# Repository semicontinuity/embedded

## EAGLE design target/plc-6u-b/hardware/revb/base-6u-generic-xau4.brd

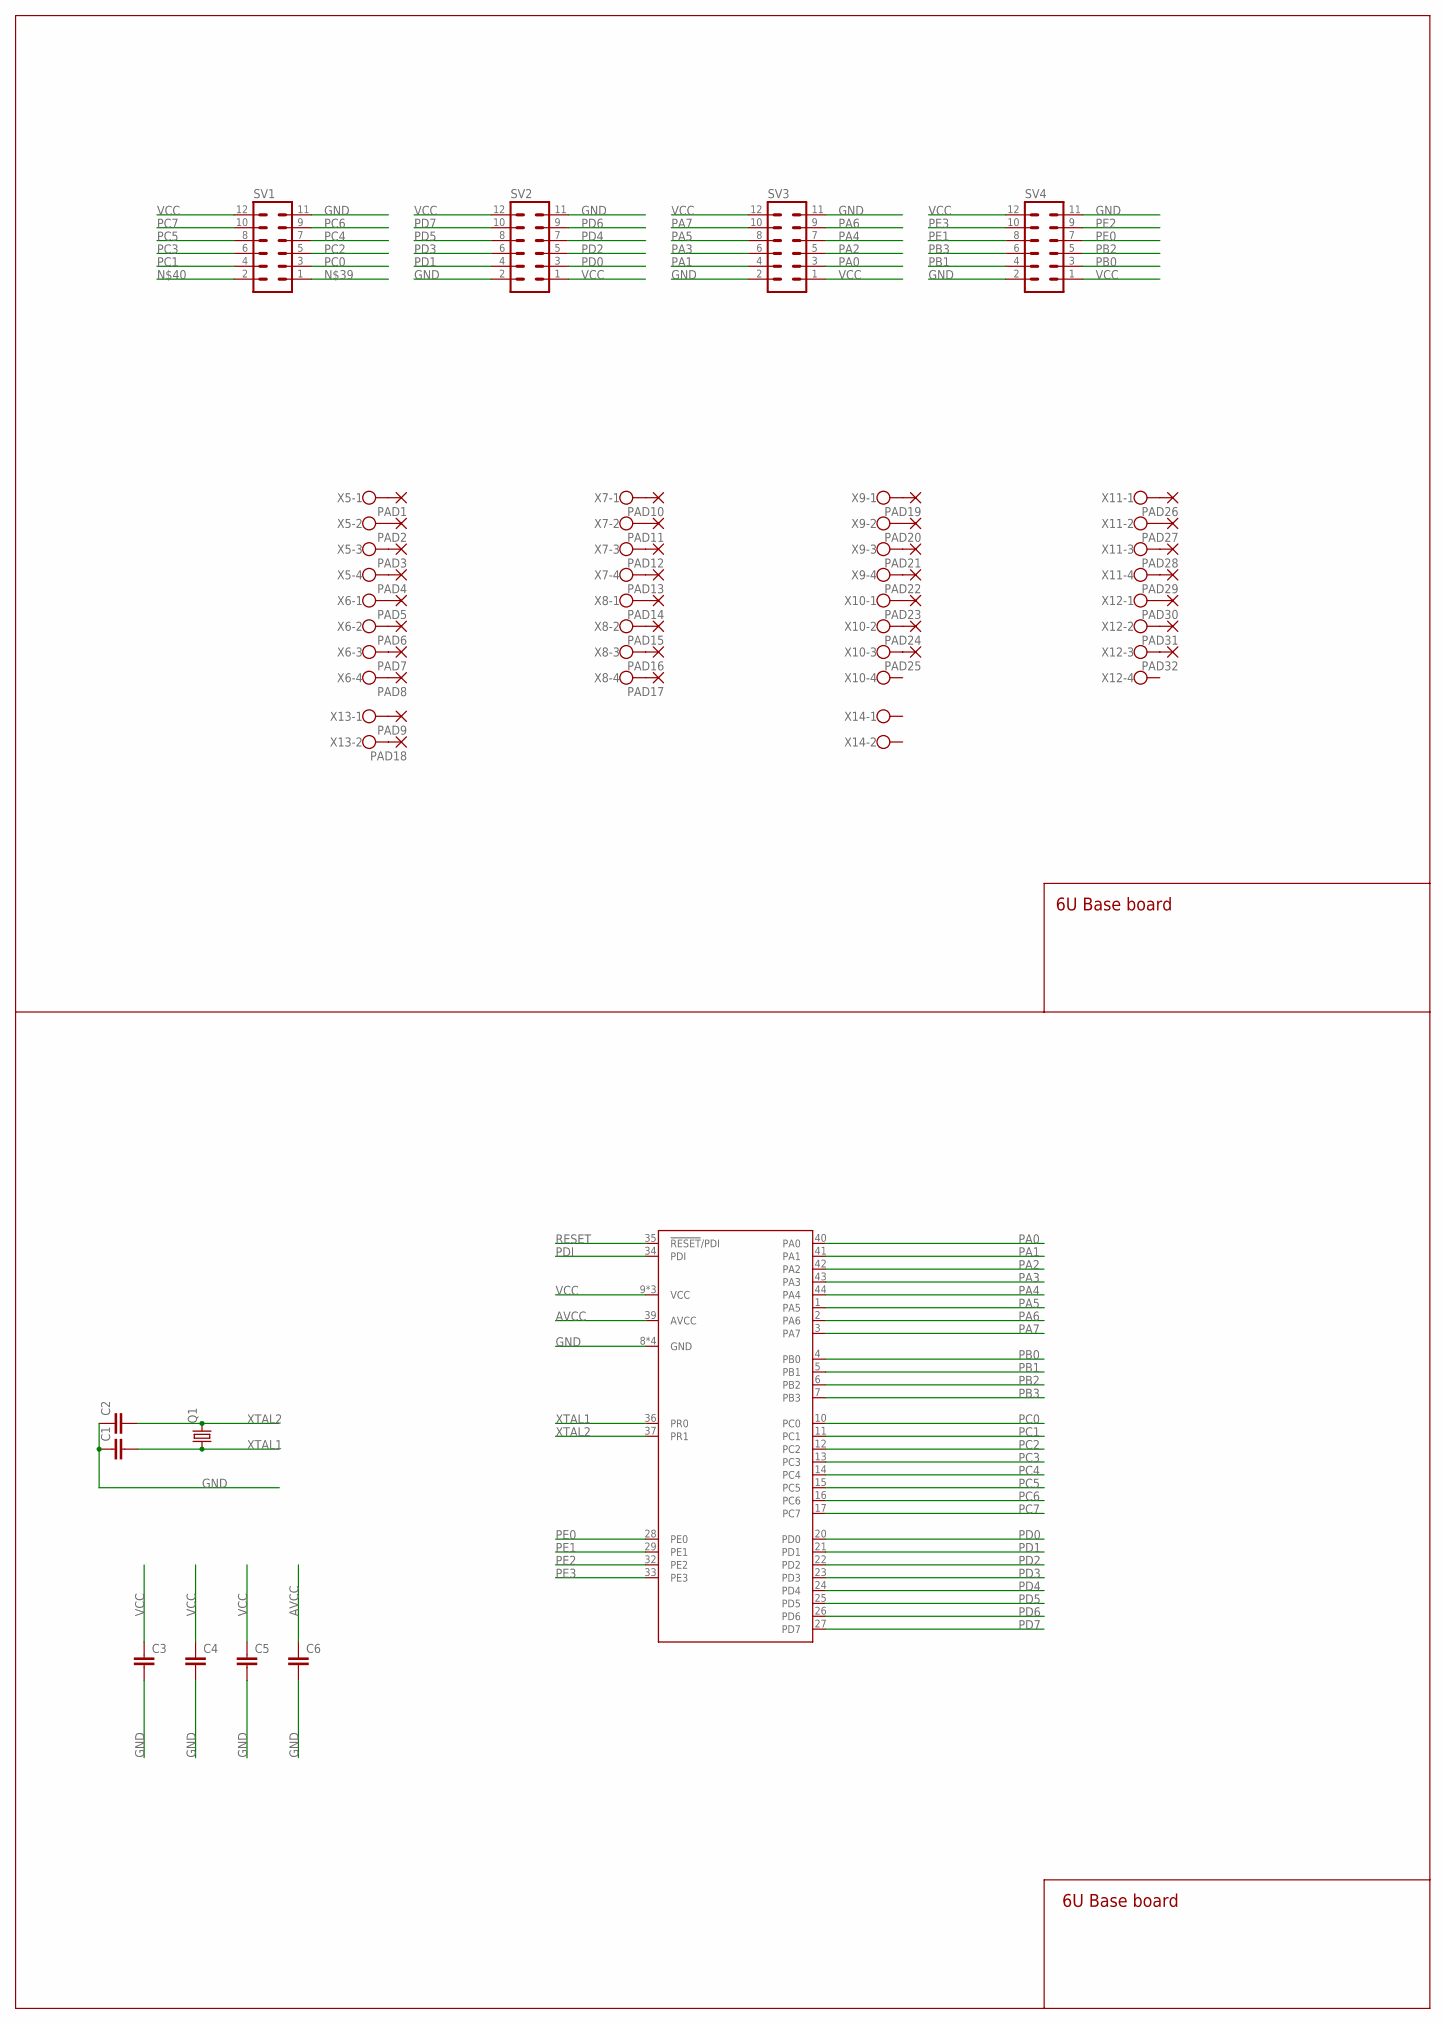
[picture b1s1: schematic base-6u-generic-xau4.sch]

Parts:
C1, C2: C-EUC0805; C0805
C3, C4, C5, C6: C-EUC0603; C0603
PAD1, PAD2, PAD3, PAD4, PAD5, PAD6, PAD7, PAD8, PAD9, PAD10, PAD11, PAD12, PAD13, PAD14, PAD15, PAD16, PAD17, PAD18, PAD19, PAD20, PAD21, PAD22, PAD23, PAD24, PAD25, PAD26, PAD27, PAD28, PAD29, PAD30, PAD31, PAD32: 2,54/0,8
Q1: CRYSTALHC49S; HC49/S
SV1, SV2, SV3, SV4: MA06-2
U1: ATXMEGA32A4U-AU; TQFP-44A-44
X5, X6, X7, X8, X9, X10, X11, X12: W237-4
X13, X14: W237-102

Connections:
AVCC: C6.1, U1.39 (AVCC)
GND: C1.1, C2.1, C3.2, C4.2, C5.2, C6.2, SV1.11, SV2.2, SV2.11, SV3.2, SV3.11, SV4.2, SV4.11, U1.8 (GND), U1.18 (GND), U1.30 (GND), U1.38 (GND)
unnamed: PAD1.1, X5.1
unnamed: PAD2.1, X5.2
unnamed: PAD3.1, X5.3
unnamed: PAD4.1, X5.4
unnamed: PAD5.1, X6.1
unnamed: PAD6.1, X6.2
unnamed: PAD7.1, X6.3
unnamed: PAD8.1, X6.4
unnamed: PAD9.1, X13.1
unnamed: PAD10.1, X7.1
unnamed: PAD11.1, X7.2
unnamed: PAD12.1, X7.3
unnamed: PAD13.1, X7.4
unnamed: PAD14.1, X8.1
unnamed: PAD15.1, X8.2
unnamed: PAD16.1, X8.3
unnamed: PAD17.1, X8.4
unnamed: PAD18.1, X13.2
unnamed: PAD26.1, X11.1
unnamed: PAD27.1, X11.2
unnamed: PAD28.1, X11.3
unnamed: PAD29.1, X11.4
unnamed: PAD30.1, X12.1
unnamed: PAD31.1, X12.2
unnamed: PAD32.1, X12.3
unnamed: PAD19.1, X9.1
unnamed: PAD20.1, X9.2
unnamed: PAD21.1, X9.3
unnamed: PAD22.1, X9.4
unnamed: PAD23.1, X10.1
unnamed: PAD24.1, X10.2
unnamed: PAD25.1, X10.3
PA0: SV3.3, U1.40 (PA0)
PA1: SV3.4, U1.41 (PA1)
PA2: SV3.5, U1.42 (PA2)
PA3: SV3.6, U1.43 (PA3)
PA4: SV3.7, U1.44 (PA4)
PA5: SV3.8, U1.1 (PA5)
PA6: SV3.9, U1.2 (PA6)
PA7: SV3.10, U1.3 (PA7)
PB0: SV4.3, U1.4 (PB0)
PB1: SV4.4, U1.5 (PB1)
PB2: SV4.5, U1.6 (PB2)
PB3: SV4.6, U1.7 (PB3)
PC0: SV1.3, U1.10 (PC0)
PC1: SV1.4, U1.11 (PC1)
PC2: SV1.5, U1.12 (PC2)
PC3: SV1.6, U1.13 (PC3)
PC4: SV1.7, U1.14 (PC4)
PC5: SV1.8, U1.15 (PC5)
PC6: SV1.9, U1.16 (PC6)
PC7: SV1.10, U1.17 (PC7)
PD0: SV2.3, U1.20 (PD0)
PD1: SV2.4, U1.21 (PD1)
PD2: SV2.5, U1.22 (PD2)
PD3: SV2.6, U1.23 (PD3)
PD4: SV2.7, U1.24 (PD4)
PD5: SV2.8, U1.25 (PD5)
PD6: SV2.9, U1.26 (PD6)
PD7: SV2.10, U1.27 (PD7)
PDI: U1.34 (PDI)
PE0: SV4.7, U1.28 (PE0)
PE1: SV4.8, U1.29 (PE1)
PE2: SV4.9, U1.32 (PE2)
PE3: SV4.10, U1.33 (PE3)
RESET: U1.35 (!RESET!/PDI)
VCC: C3.1, C4.1, C5.1, SV1.12, SV2.1, SV2.12, SV3.1, SV3.12, SV4.1, SV4.12, U1.9 (VCC), U1.19 (VCC), U1.31 (VCC)
XTAL1: C1.2, Q1.1, U1.36 (PR0)
XTAL2: C2.2, Q1.2, U1.37 (PR1)

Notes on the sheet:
6U Base board

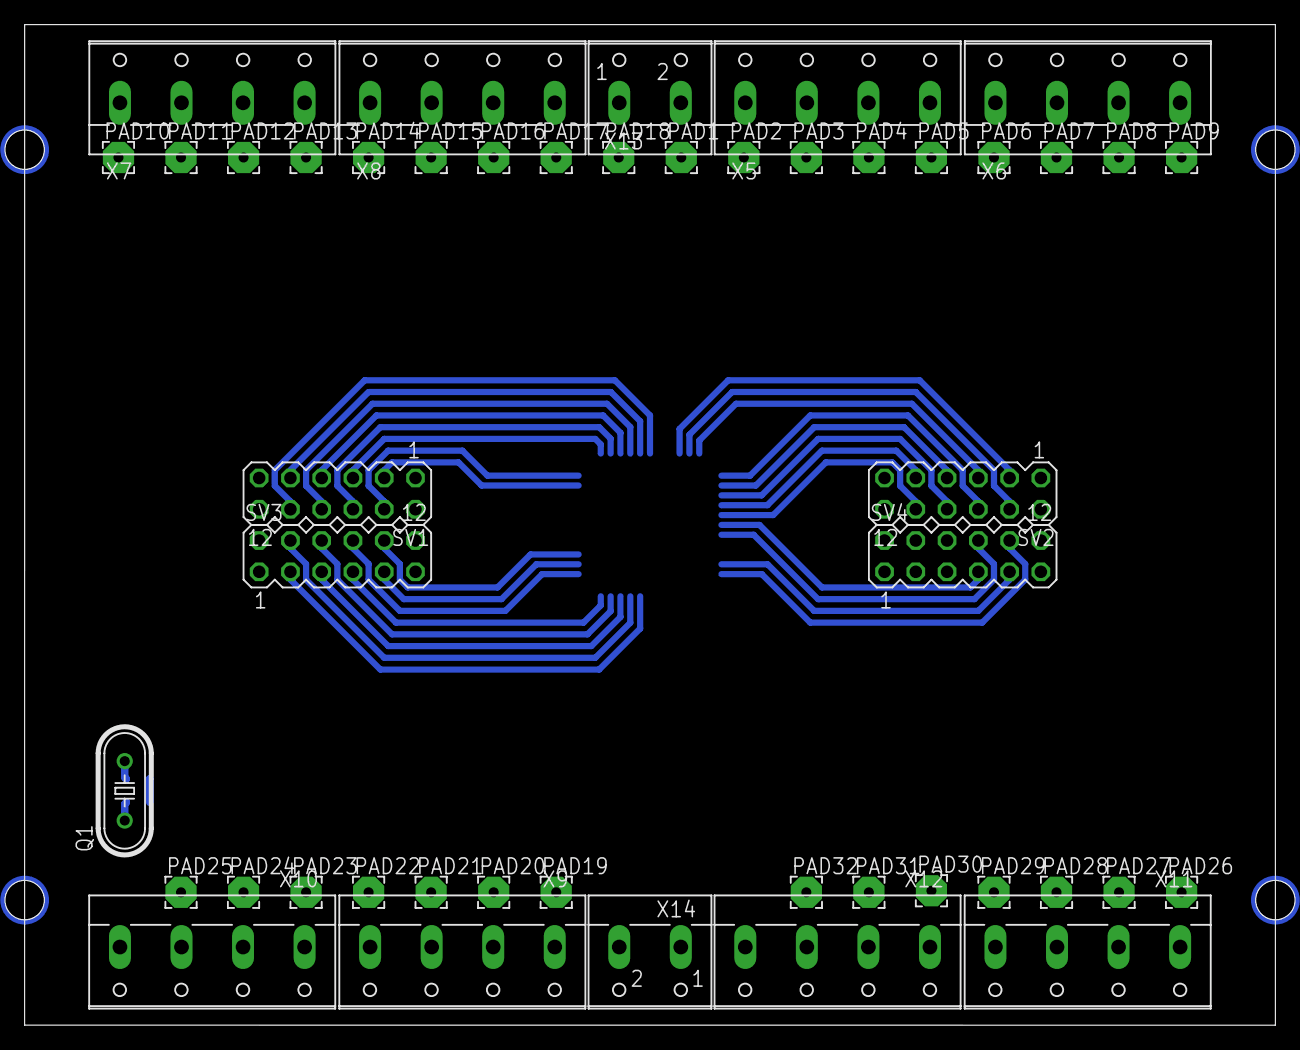
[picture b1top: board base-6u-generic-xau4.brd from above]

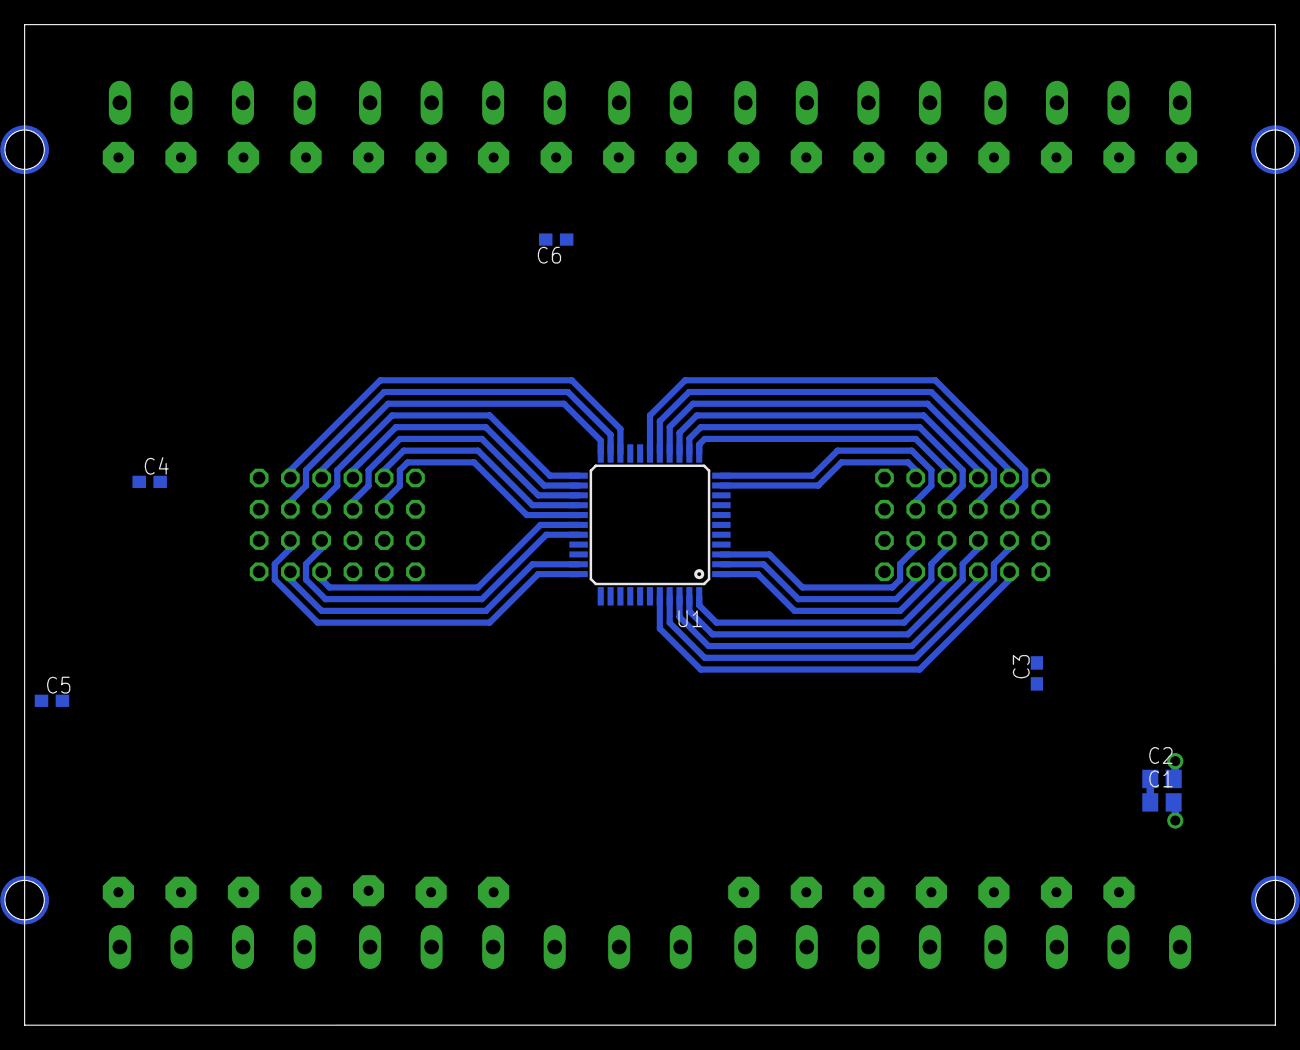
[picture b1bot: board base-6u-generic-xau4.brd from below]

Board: 2 copper layers, 101.6 x 81.3 mm, 54 parts (7 on the bottom side), 69 nets.

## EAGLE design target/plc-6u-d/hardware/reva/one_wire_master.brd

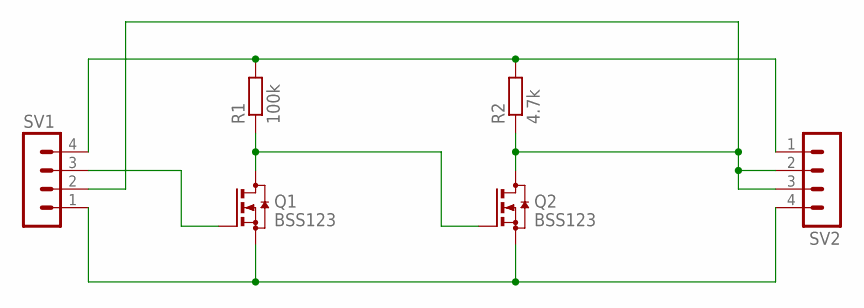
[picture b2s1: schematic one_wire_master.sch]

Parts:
Q1, Q2: BSS123; SOT23
R1: 100k; M0805
R2: 4.7k; M0805
SV1, SV2: MA04-1

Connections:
GND: Q1.2 (S), Q2.2 (S), SV1.1, SV2.4
IN: Q1.1 (G), SV1.3
unnamed: Q1.3 (D), Q2.1 (G), R1.1
OW: Q2.3 (D), R2.1, SV1.2, SV2.2, SV2.3
VCC: R1.2, R2.2, SV1.4, SV2.1

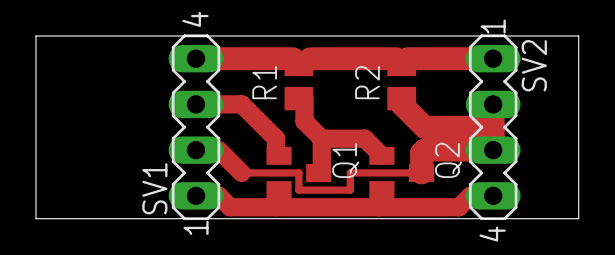
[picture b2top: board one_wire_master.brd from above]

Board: 2 copper layers, 30.1 x 10.2 mm, 6 parts (0 on the bottom side), 5 nets.

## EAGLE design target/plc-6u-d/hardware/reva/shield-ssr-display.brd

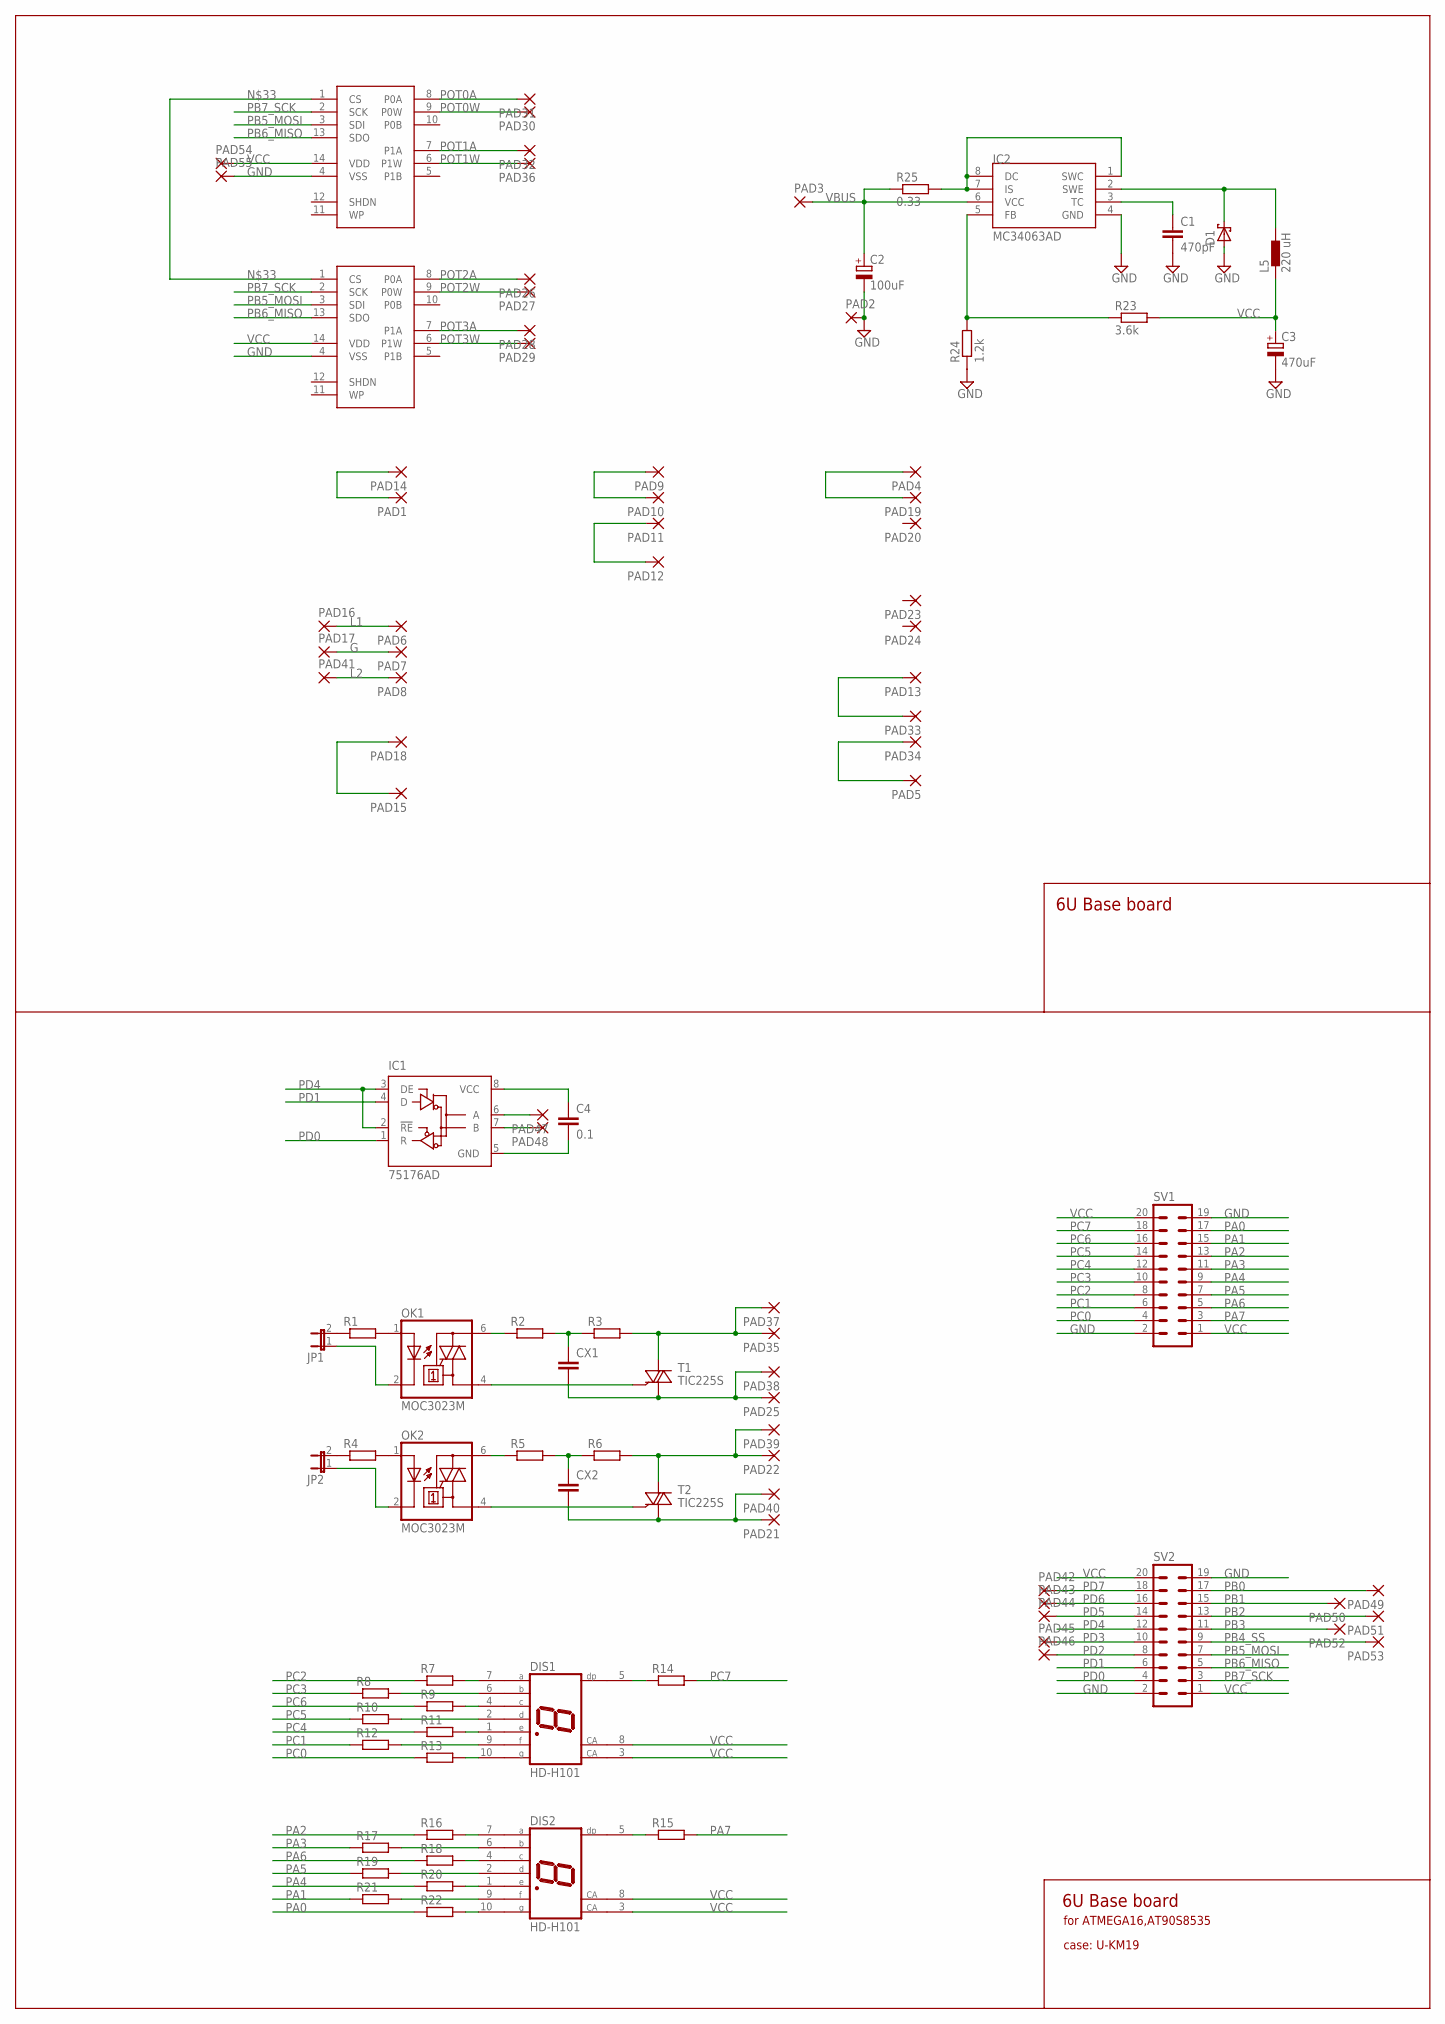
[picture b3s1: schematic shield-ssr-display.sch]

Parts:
C1: 470pF; C0805
C2: 100uF; E3,5-8
C3: 470uF; E3,5-8
C4: 0.1; C0805
CX1, CX2: CXXC15B5; XC15B5
D1: SCHOTTKY-DIODESMD; SMB
DIS1, DIS2: HD-H101; HDSP-M
IC1: 75176AD; D_R-PDSO-G8
IC2: MC34063AD; SOIC8
JP1, JP2: JP1E; JP1
L5: 220 uH; DR1030
OK1, OK2: MOC3023M; DIL06
PAD1, PAD2, PAD3, PAD4, PAD5, PAD6, PAD7, PAD8, PAD9, PAD10, PAD11, PAD12, PAD13, PAD14, PAD15, PAD16, PAD17, PAD18, PAD19, PAD20, PAD21, PAD22, PAD23, PAD24, PAD25, PAD26, PAD27, PAD28, PAD29, PAD30, PAD31, PAD32, PAD33, PAD34, PAD35, PAD36, PAD37, PAD38, PAD39, PAD40, PAD41: 2,54/0,8
PAD42, PAD43, PAD44, PAD45, PAD46, PAD47, PAD48, PAD49, PAD50, PAD51, PAD52, PAD53, PAD54, PAD55: 1,6/0,8
R1, R4: R-EU_M0805; M0805
R2, R3, R5, R6: R-EU_R1206; R1206
R7, R8, R9, R10, R11, R12, R13, R14, R15, R16, R17, R18, R19, R20, R21, R22: R-EU_R0603; R0603
R23: 3.6k; R0805
R24: 1.2k; R0805
R25: 0.33; R1206
SV1, SV2: MA10-2
T1, T2: TIC225S; TO220DS
U$1, U$2: MCP4231-DIP; DIL14

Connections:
G: PAD7.1, PAD17.1
GND: C1.2, C2.-, C3.-, C4.2, D1.A, IC1.5 (GND), IC2.4 (GND), PAD2.1, PAD4.1, PAD19.1, PAD55.1, R24.1, SV1.2, SV1.19, SV2.2, SV2.19, U$1.4 (VSS), U$2.4 (VSS)
L1: PAD6.1, PAD16.1
L2: PAD8.1, PAD41.1
unnamed: OK1.1 (A), R1.2
unnamed: JP1.2, R1.1
unnamed: JP1.1, OK1.2 (C)
unnamed: OK1.6 (A2), R2.1
unnamed: CX1.1, R2.2, R3.1
unnamed: OK1.4 (A1), T1.G
unnamed: PAD35.1, PAD37.1, R3.2, T1.A2
unnamed: CX1.2, PAD25.1, PAD38.1, T1.A1
unnamed: OK2.1 (A), R4.2
unnamed: JP2.2, R4.1
unnamed: JP2.1, OK2.2 (C)
unnamed: OK2.6 (A2), R5.1
unnamed: OK2.4 (A1), T2.G
unnamed: PAD22.1, PAD39.1, R6.2, T2.A2
unnamed: DIS1.7 (A), R7.2
unnamed: CX2.1, R5.2, R6.1
unnamed: CX2.2, PAD21.1, PAD40.1, T2.A1
unnamed: DIS1.6 (B), R8.2
unnamed: DIS1.4 (C), R9.2
unnamed: DIS1.2 (D), R10.2
unnamed: DIS1.1 (E), R11.2
unnamed: DIS1.9 (F), R12.2
unnamed: DIS1.10 (G), R13.2
unnamed: DIS1.5 (DP), R14.1
unnamed: DIS2.7 (A), R16.2
unnamed: DIS2.6 (B), R17.2
unnamed: DIS2.4 (C), R18.2
unnamed: DIS2.2 (D), R19.2
unnamed: DIS2.1 (E), R20.2
unnamed: DIS2.9 (F), R21.2
unnamed: DIS2.10 (G), R22.2
unnamed: DIS2.5 (DP), R15.1
unnamed: U$1.1 (CS), U$2.1 (CS)
unnamed: IC2.1 (SWC), IC2.7 (IS), IC2.8 (DC), R25.2
unnamed: PAD9.1, PAD10.1
unnamed: PAD11.1, PAD12.1
unnamed: D1.C, IC2.2 (SWE), L5.2
unnamed: C1.1, IC2.3 (TC)
unnamed: IC1.6 (A), PAD47.1
unnamed: IC2.5 (FB), R23.1, R24.2
unnamed: PAD13.1, PAD33.1
unnamed: PAD15.1, PAD18.1
unnamed: PAD1.1, PAD14.1
unnamed: IC1.7 (B), PAD48.1
PA0: R22.1, SV1.17
PA1: R21.1, SV1.15
PA2: R16.1, SV1.13
PA3: R17.1, SV1.11
PA4: R20.1, SV1.9
PA5: R19.1, SV1.7
PA6: R18.1, SV1.5
PA7: R15.2, SV1.3
PB0: PAD49.1, SV2.17
PB1: PAD50.1, SV2.15
PB2: PAD51.1, SV2.13
PB3: PAD52.1, SV2.11
PB4_SS: PAD53.1, SV2.9
PB5_MOSI: SV2.7, U$1.3 (SDI), U$2.3 (SDI)
PB6_MISO: SV2.5, U$1.13 (SDO), U$2.13 (SDO)
PB7_SCK: SV2.3, U$1.2 (SCK), U$2.2 (SCK)
PC0: R13.1, SV1.4
PC1: R12.1, SV1.6
PC2: R7.1, SV1.8
PC3: R8.1, SV1.10
PC4: R11.1, SV1.12
PC5: R10.1, SV1.14
PC6: R9.1, SV1.16
PC7: R14.2, SV1.18
PD0: IC1.1 (R), SV2.4
PD1: IC1.4 (D), SV2.6
PD2: PAD46.1, SV2.8
PD3: PAD45.1, SV2.10
PD4: IC1.2 (!RE), IC1.3 (DE), SV2.12
PD5: PAD44.1, SV2.14
PD6: PAD43.1, SV2.16
PD7: PAD42.1, SV2.18
POT0A: PAD31.1, U$1.8 (P0A)
POT0W: PAD30.1, U$1.9 (P0W)
POT1A: PAD32.1, U$1.7 (P1A)
POT1W: PAD36.1, U$1.6 (P1W)
POT2A: PAD26.1, U$2.8 (P0A)
POT2W: PAD27.1, U$2.9 (P0W)
POT3A: PAD28.1, U$2.7 (P1A)
POT3W: PAD29.1, U$2.6 (P1W)
VBUS: C2.+, IC2.6 (VCC), PAD3.1, R25.1
VCC: C3.+, C4.1, DIS1.3 (CA), DIS1.8 (CA), DIS2.3 (CA), DIS2.8 (CA), IC1.8 (VCC), L5.1, PAD5.1, PAD34.1, PAD54.1, R23.2, SV1.1, SV1.20, SV2.1, SV2.20, U$1.14 (VDD), U$2.14 (VDD)

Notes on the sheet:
6U Base board
for ATMEGA16,AT90S8535
case: U-KM19

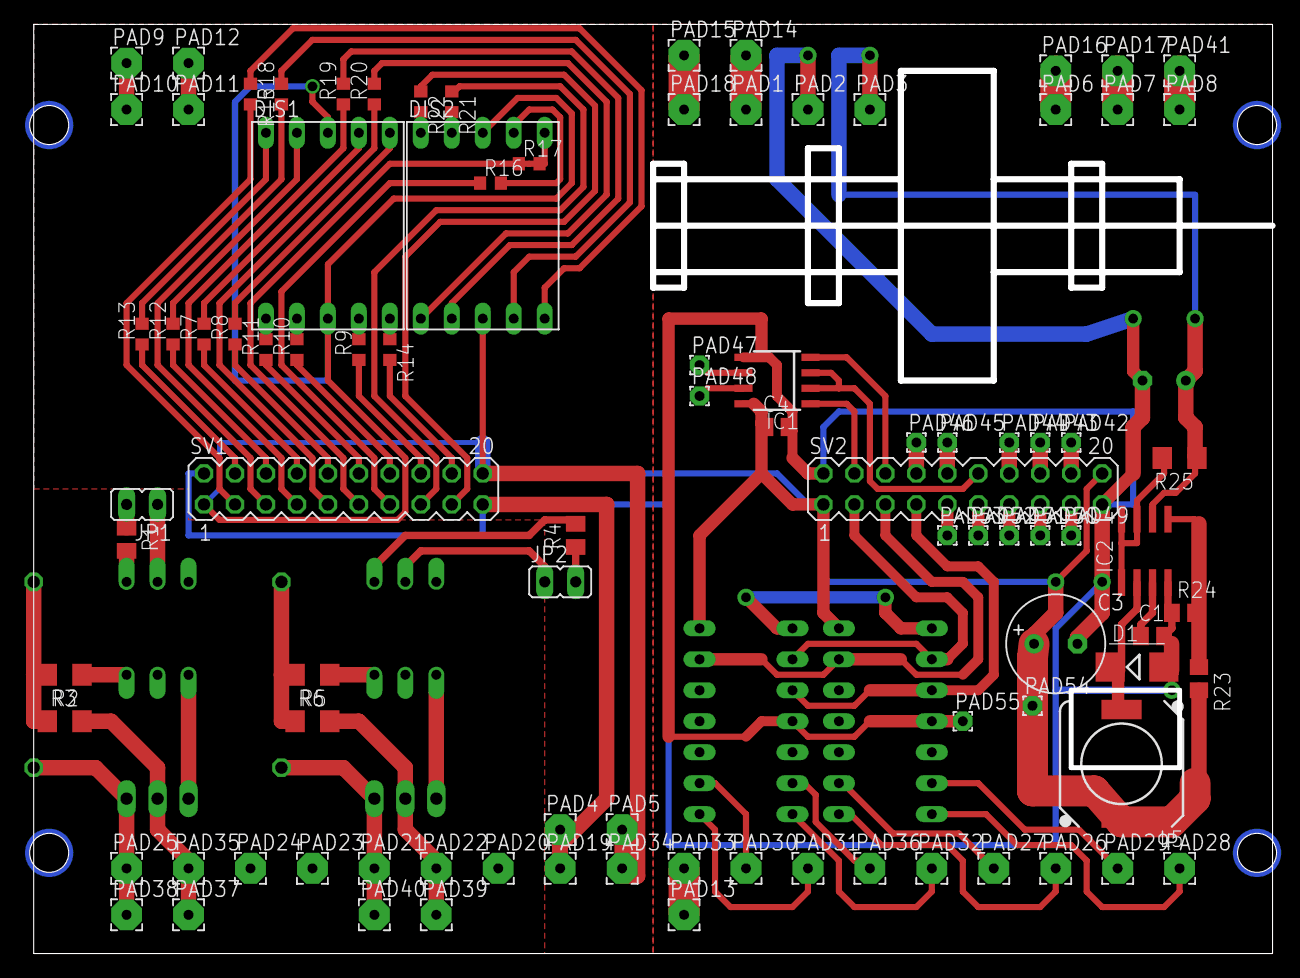
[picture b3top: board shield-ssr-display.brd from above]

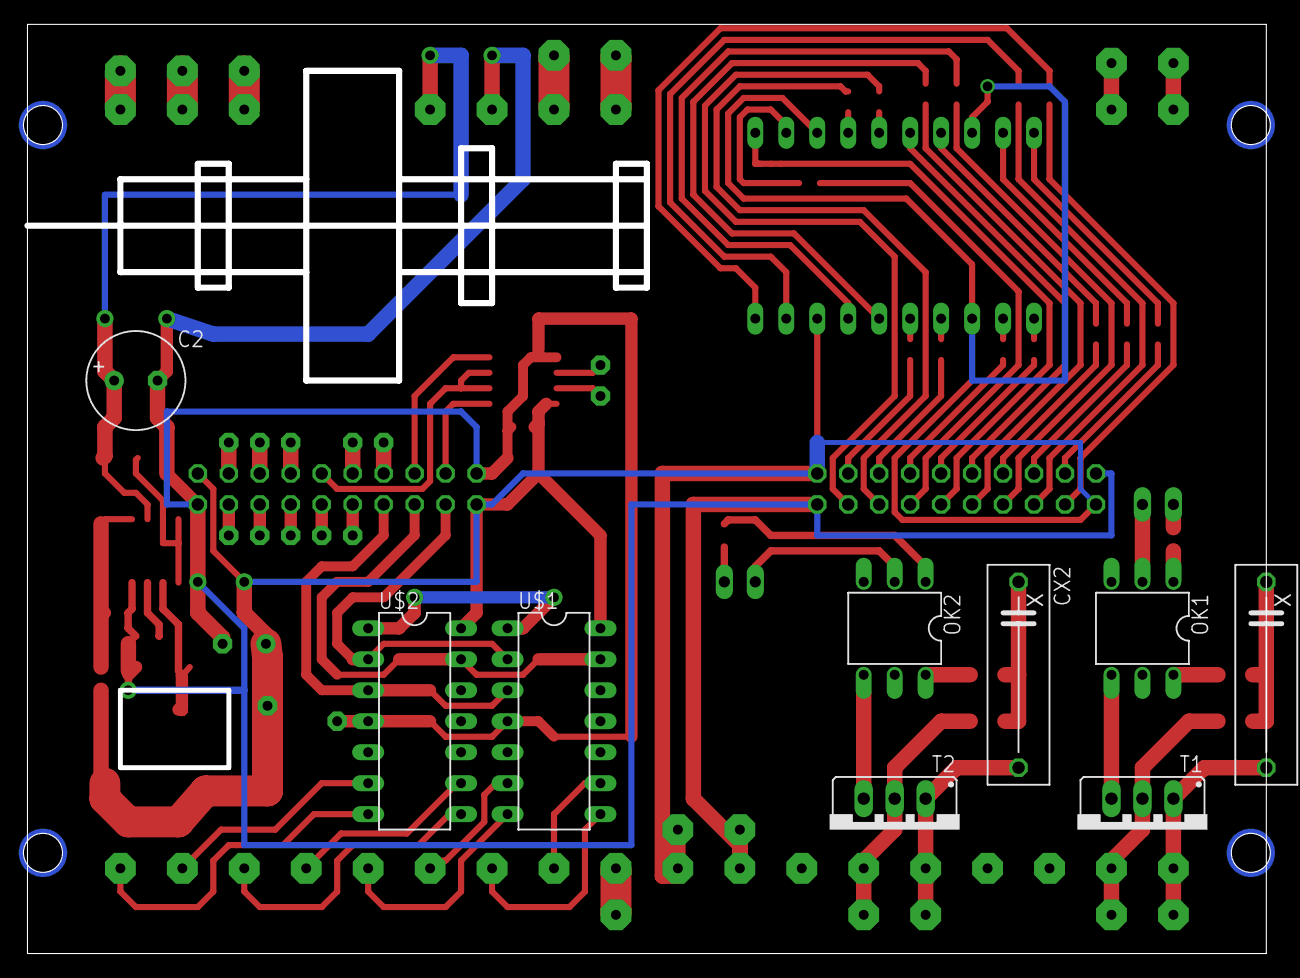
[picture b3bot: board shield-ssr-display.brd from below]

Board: 2 copper layers, 101.6 x 76.2 mm, 102 parts (9 on the bottom side), 90 nets.

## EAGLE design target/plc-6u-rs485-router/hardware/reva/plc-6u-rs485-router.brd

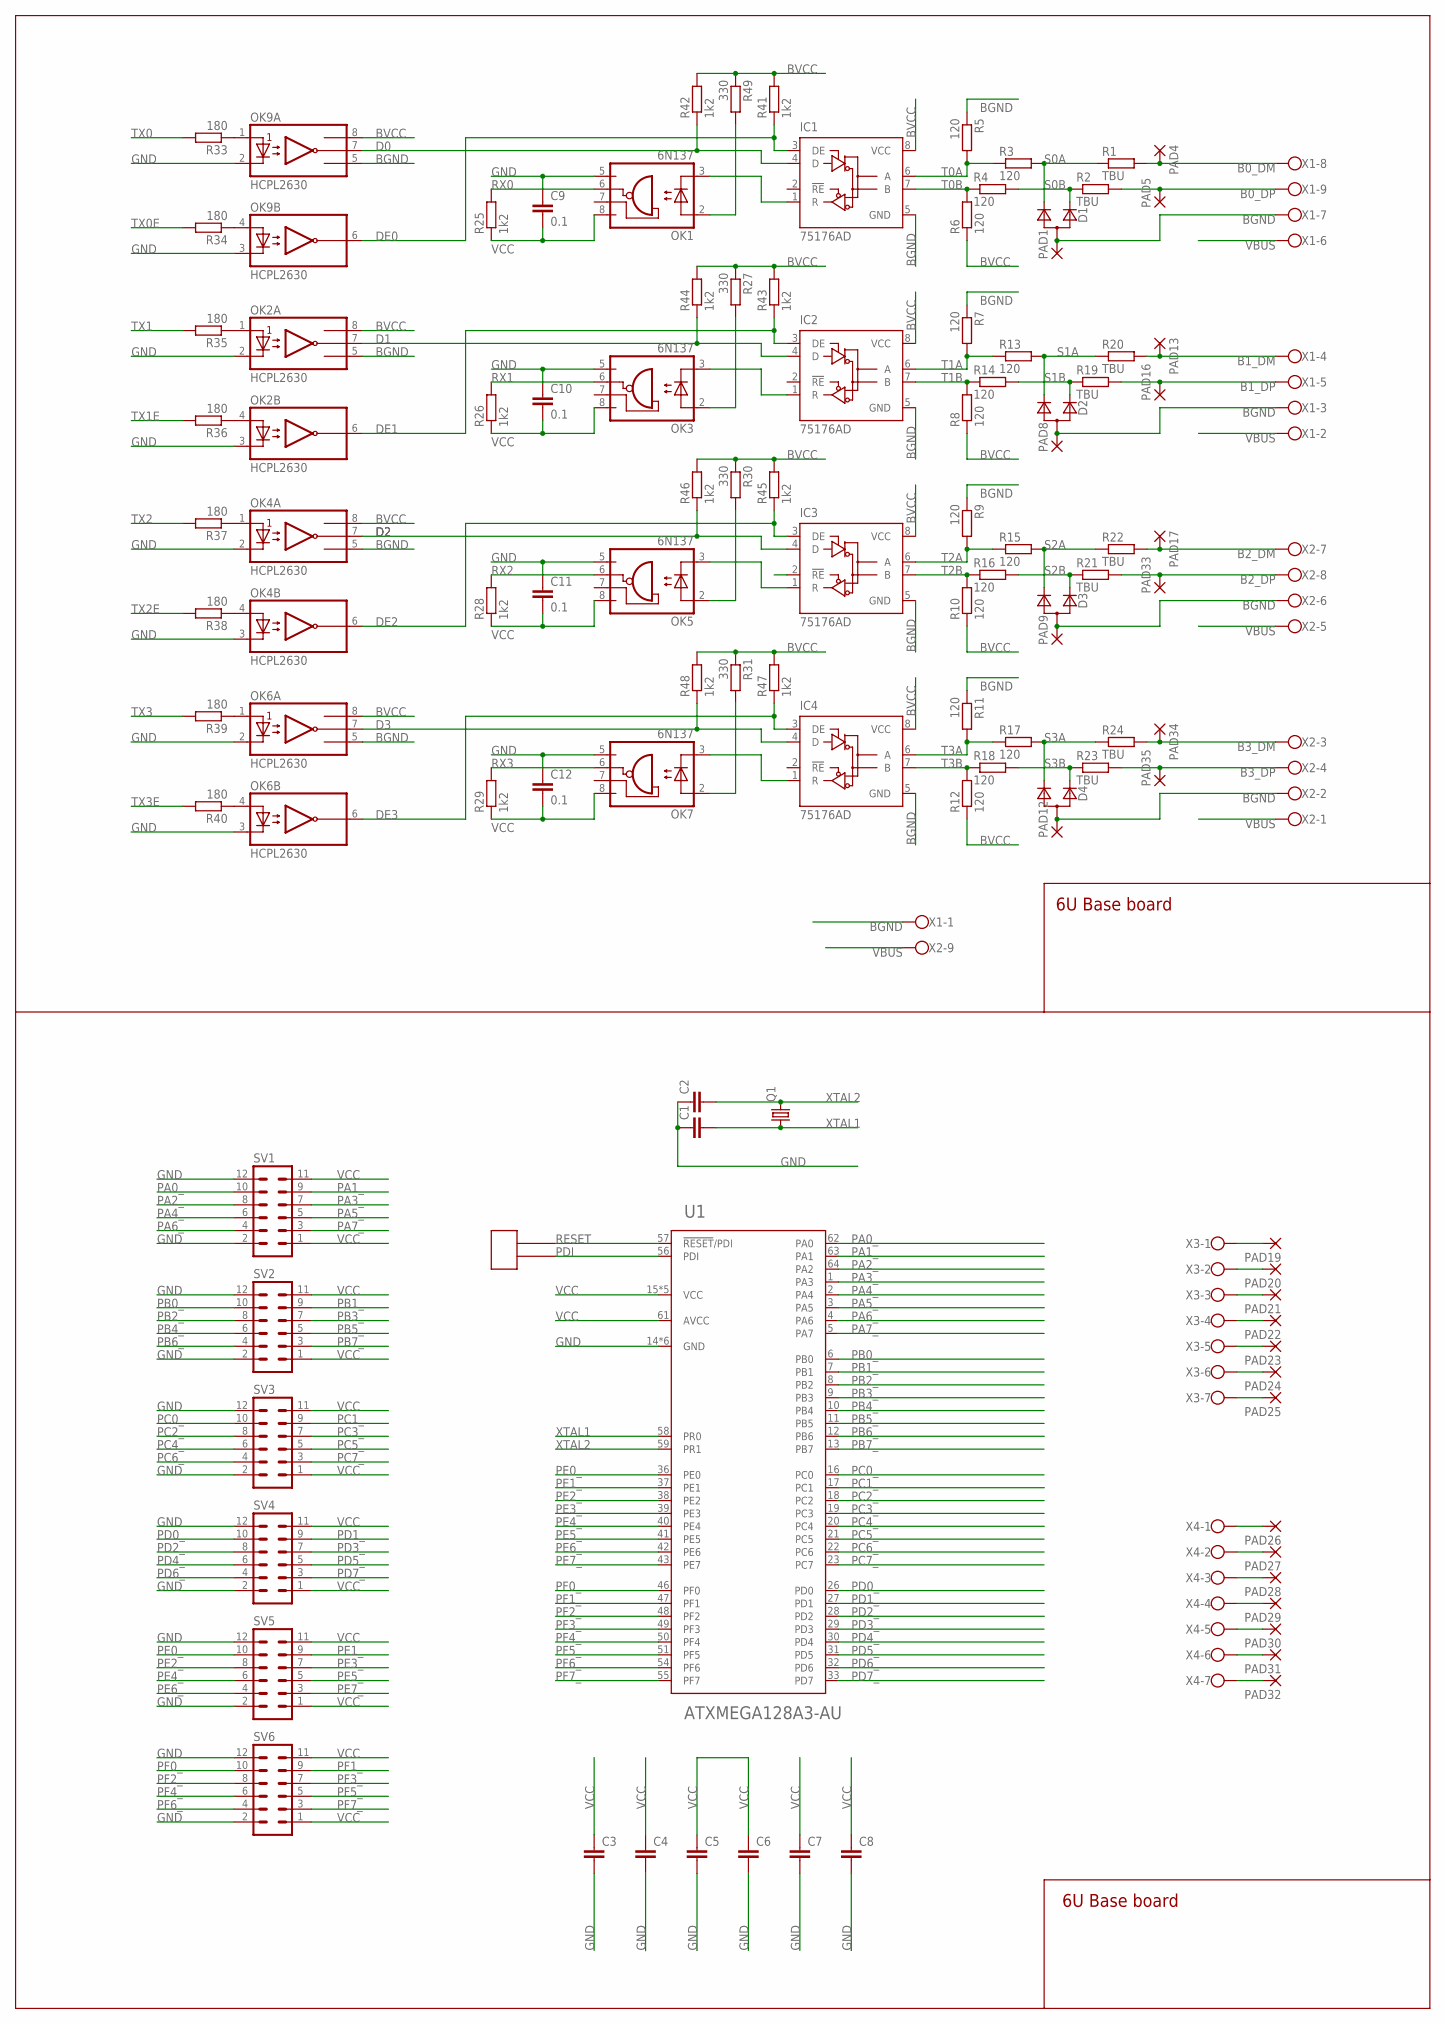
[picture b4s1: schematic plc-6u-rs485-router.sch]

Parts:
C1, C2: C-EUC0805; C0805
C3, C4, C5, C6, C7, C8: C-EUC0603; C0603
C9, C10, C11, C12: 0.1; C0805
D1, D2, D3, D4: D_2CSOT323; SOT323
IC1, IC2, IC3, IC4: 75176AD; D_R-PDSO-G8
OK1, OK3, OK5, OK7: 6N137; DIL08
OK2, OK4, OK6, OK9: HCPL2630; DIL08
PAD1, PAD4, PAD5, PAD8, PAD9, PAD12, PAD13, PAD16, PAD17, PAD19, PAD20, PAD21, PAD22, PAD23, PAD24, PAD25, PAD26, PAD27, PAD28, PAD29, PAD30, PAD31, PAD32, PAD33, PAD34, PAD35: 2,54/0,8
Q1: CRYSTALHC49S; HC49/S
R1, R2, R19, R20, R21, R22, R23, R24: TBU; WSC2515
R3, R4, R5, R6, R7, R8, R9, R10, R11, R12, R13, R14, R15, R16, R17, R18: 120; R0805
R25, R26, R28, R29, R41, R42, R43, R44, R45, R46, R47, R48: 1k2; R0805
R27, R30, R31, R49: 330; R0805
R33, R34, R35, R36, R37, R38, R39, R40: 180; R0805
SV1, SV2, SV3, SV4, SV5, SV6: MA06-2
U1: ATXMEGA128A3-AU; TQFP-64A-64
U$1: MA02-1
X1, X2: W237-09P; W237-9P
X3, X4: W237-07P; W237-7P

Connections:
B0_DM: PAD4.1, R1.2, X1.8
B0_DP: PAD5.1, R2.2, X1.9
B1_DM: PAD16.1, R19.2, X1.5
B1_DP: PAD13.1, R20.2, X1.4
B2_DM: PAD17.1, R22.2, X2.7
B2_DP: PAD33.1, R21.2, X2.8
B3_DM: PAD34.1, R24.2, X2.3
B3_DP: PAD35.1, R23.2, X2.4
BGND: D1.1 (A), D2.1 (A), D3.1 (A), D4.1 (A), IC1.5 (GND), IC2.5 (GND), IC3.5 (GND), IC4.5 (GND), OK2.5 (GND), OK4.5 (GND), OK6.5 (GND), OK9.5 (GND), PAD1.1, PAD8.1, PAD9.1, PAD12.1, R5.1, R7.1, R9.1, R11.1, X1.1, X1.3, X1.7, X2.2, X2.6
BVCC: IC1.8 (VCC), IC2.8 (VCC), IC3.8 (VCC), IC4.8 (VCC), OK2.8 (VCC), OK4.8 (VCC), OK6.8 (VCC), OK9.8 (VCC), R6.1, R8.1, R10.1, R12.1, R27.1, R30.1, R31.1, R41.2, R42.2, R43.2, R44.2, R45.2, R46.2, R47.2, R48.2, R49.1
D0: IC1.4 (D), OK9.7 (VO1), R42.1
D1: IC2.4 (D), OK2.7 (VO1), R44.1
D2: IC3.4 (D), OK4.7 (VO1), R46.1
D3: IC4.4 (D), OK6.7 (VO1), R48.1
DE0: IC1.3 (DE), OK9.6 (VO2), R41.1
DE1: IC2.3 (DE), OK2.6 (VO2), R43.1
DE2: IC3.3 (DE), OK4.6 (VO2), R45.1
DE3: IC4.3 (DE), OK6.6 (VO2), R47.1
GND: C1.1, C2.1, C3.2, C4.2, C5.2, C6.2, C7.2, C8.2, C9.1, C10.1, C11.1, C12.1, OK1.5 (GND), OK2.2 (C1), OK2.3 (C2), OK3.5 (GND), OK4.2 (C1), OK4.3 (C2), OK5.5 (GND), OK6.2 (C1), OK6.3 (C2), OK7.5 (GND), OK9.2 (C1), OK9.3 (C2), SV1.2, SV1.12, SV2.2, SV2.12, SV3.2, SV3.12, SV4.2, SV4.12, SV5.2, SV5.12, SV6.2, SV6.12, U1.14 (GND), U1.24 (GND), U1.34 (GND), U1.44 (GND), U1.52 (GND), U1.60 (GND)
unnamed: OK7.2 (A), R31.2
unnamed: OK5.2 (A), R30.2
unnamed: OK3.2 (A), R27.2
unnamed: OK1.2 (A), R49.2
unnamed: OK2.1 (A1), R35.1
unnamed: OK2.4 (A2), R36.1
unnamed: OK4.1 (A1), R37.1
unnamed: OK9.1 (A1), R33.1
unnamed: OK4.4 (A2), R38.1
unnamed: OK6.1 (A1), R39.1
unnamed: OK9.4 (A2), R34.1
unnamed: OK6.4 (A2), R40.1
unnamed: PAD19.1, X3.1
unnamed: PAD20.1, X3.2
unnamed: PAD21.1, X3.3
unnamed: PAD22.1, X3.4
unnamed: PAD23.1, X3.5
unnamed: PAD24.1, X3.6
unnamed: PAD25.1, X3.7
unnamed: PAD26.1, X4.1
unnamed: PAD27.1, X4.2
unnamed: PAD28.1, X4.3
unnamed: PAD29.1, X4.4
unnamed: PAD30.1, X4.5
unnamed: PAD31.1, X4.6
unnamed: PAD32.1, X4.7
PA0_: SV1.10, U1.62 (PA0)
PA1_: SV1.9, U1.63 (PA1)
PA2_: SV1.8, U1.64 (PA2)
PA3_: SV1.7, U1.1 (PA3)
PA4_: SV1.6, U1.2 (PA4)
PA5_: SV1.5, U1.3 (PA5)
PA6_: SV1.4, U1.4 (PA6)
PA7_: SV1.3, U1.5 (PA7)
PB0_: SV2.10, U1.6 (PB0)
PB1_: SV2.9, U1.7 (PB1)
PB2_: SV2.8, U1.8 (PB2)
PB3_: SV2.7, U1.9 (PB3)
PB4_: SV2.6, U1.10 (PB4)
PB5_: SV2.5, U1.11 (PB5)
PB6_: SV2.4, U1.12 (PB6)
PB7_: SV2.3, U1.13 (PB7)
PC0_: SV3.10, U1.16 (PC0)
PC1_: SV3.9, U1.17 (PC1)
PC2_: SV3.8, U1.18 (PC2)
PC3_: SV3.7, U1.19 (PC3)
PC4_: SV3.6, U1.20 (PC4)
PC5_: SV3.5, U1.21 (PC5)
PC6_: SV3.4, U1.22 (PC6)
PC7_: SV3.3, U1.23 (PC7)
PD0_: SV4.10, U1.26 (PD0)
PD1_: SV4.9, U1.27 (PD1)
PD2_: SV4.8, U1.28 (PD2)
PD3_: SV4.7, U1.29 (PD3)
PD4_: SV4.6, U1.30 (PD4)
PD5_: SV4.5, U1.31 (PD5)
PD6_: SV4.4, U1.32 (PD6)
PD7_: SV4.3, U1.33 (PD7)
PDI: U1.56 (PDI), U$1.P1
PE0_: SV5.10, U1.36 (PE0)
PE1_: SV5.9, U1.37 (PE1)
PE2_: SV5.8, U1.38 (PE2)
PE3_: SV5.7, U1.39 (PE3)
PE4_: SV5.6, U1.40 (PE4)
PE5_: SV5.5, U1.41 (PE5)
PE6_: SV5.4, U1.42 (PE6)
PE7_: SV5.3, U1.43 (PE7)
PF0_: SV6.10, U1.46 (PF0)
PF1_: SV6.9, U1.47 (PF1)
PF2_: SV6.8, U1.48 (PF2)
PF3_: SV6.7, U1.49 (PF3)
PF4_: SV6.6, U1.50 (PF4)
PF5_: SV6.5, U1.51 (PF5)
PF6_: SV6.4, U1.54 (PF6)
PF7_: SV6.3, U1.55 (PF7)
R0: IC1.1 (R), OK1.3 (C)
R1: IC2.1 (R), OK3.3 (C)
R2: IC3.1 (R), OK5.3 (C)
R3: IC4.1 (R), OK7.3 (C)
RESET: U1.57 (!RESET!/PDI), U$1.P2
RX0: OK1.6 (VO), R25.2
RX1: OK3.6 (VO), R26.2
RX2: OK5.6 (VO), R28.2
RX3: OK7.6 (VO), R29.2
S0A: D1.3 (C2), R1.1, R3.2
S0B: D1.2 (C1), R2.1, R4.2
S1A: D2.3 (C2), R13.2, R20.1
S1B: D2.2 (C1), R14.2, R19.1
S2A: D3.3 (C2), R15.2, R22.1
S2B: D3.2 (C1), R16.2, R21.1
S3A: D4.3 (C2), R17.2, R24.1
S3B: D4.2 (C1), R18.2, R23.1
T0A: IC1.6 (A), R3.1, R5.2
T0B: IC1.7 (B), R4.1, R6.2
T1A: IC2.6 (A), R7.2, R13.1
T1B: IC2.7 (B), R8.2, R14.1
T2A: IC3.6 (A), R9.2, R15.1
T2B: IC3.7 (B), R10.2, R16.1
T3A: IC4.6 (A), R11.2, R17.1
T3B: IC4.7 (B), R12.2, R18.1
TX0: R33.2
TX0E: R34.2
TX1: R35.2
TX1E: R36.2
TX2: R37.2
TX2E: R38.2
TX3: R39.2
TX3E: R40.2
VBUS: X1.2, X1.6, X2.1, X2.5, X2.9
VCC: C3.1, C4.1, C5.1, C6.1, C7.1, C8.1, C9.2, C10.2, C11.2, C12.2, OK1.8 (VCC), OK3.8 (VCC), OK5.8 (VCC), OK7.8 (VCC), R25.1, R26.1, R28.1, R29.1, SV1.1, SV1.11, SV2.1, SV2.11, SV3.1, SV3.11, SV4.1, SV4.11, SV5.1, SV5.11, SV6.1, SV6.11, U1.15 (VCC), U1.25 (VCC), U1.35 (VCC), U1.45 (VCC), U1.53 (VCC), U1.61 (AVCC)
XTAL1: C1.2, Q1.1, U1.58 (PR0)
XTAL2: C2.2, Q1.2, U1.59 (PR1)

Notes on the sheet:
6U Base board
